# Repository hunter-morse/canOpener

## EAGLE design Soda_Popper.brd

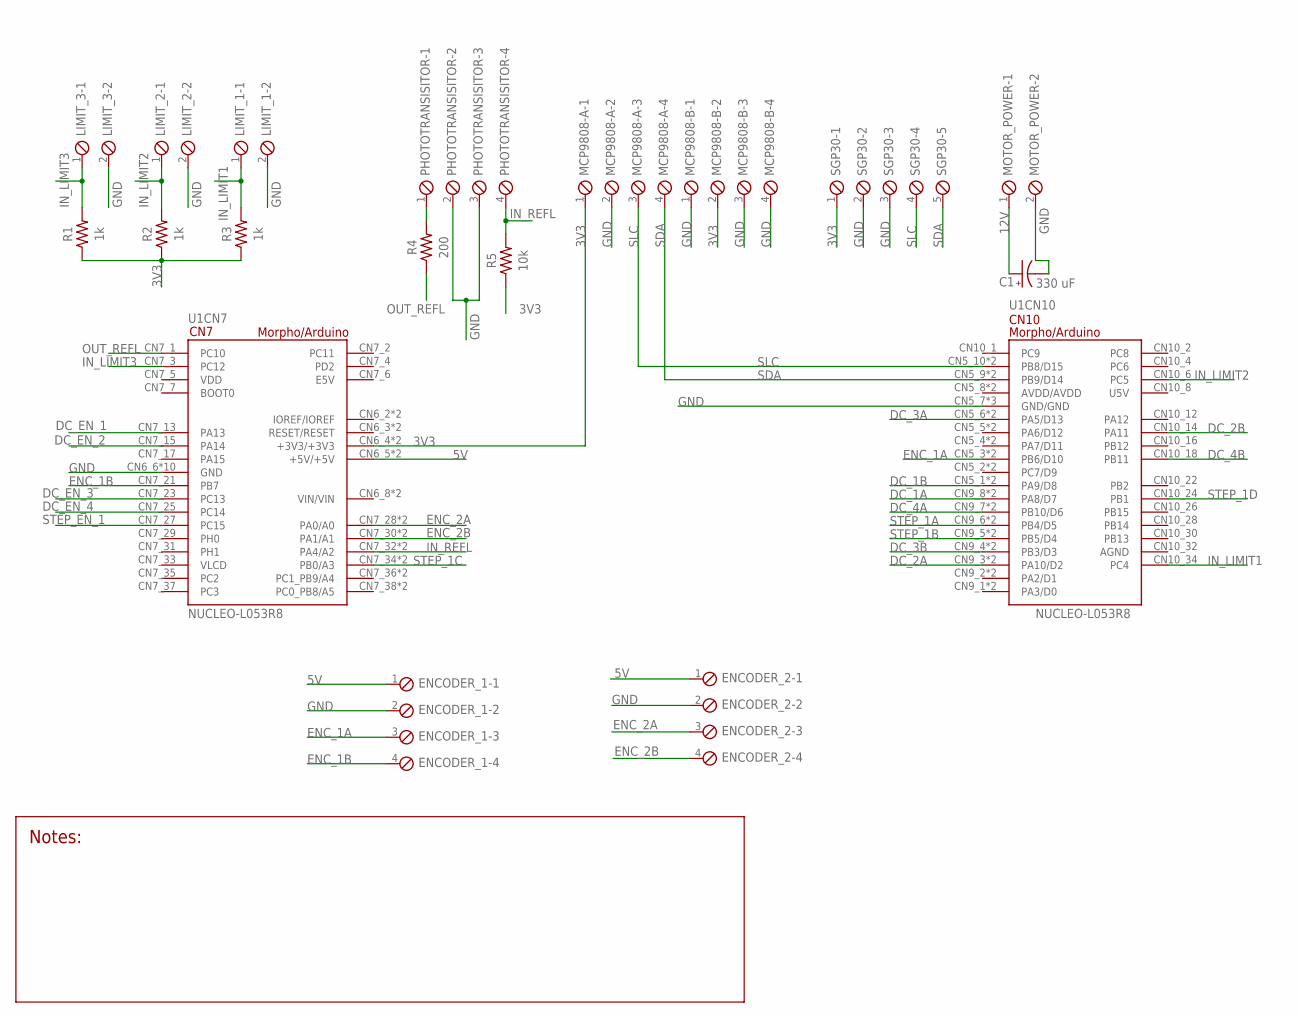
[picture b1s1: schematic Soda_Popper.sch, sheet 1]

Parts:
C1: 330 uF; CAPPRD508W65D1000H1100B
ENCODER_1, ENCODER_2: SCREWTERM_4P_254; 4POL254
LIMIT_1, LIMIT_2, LIMIT_3: SCREWTERM_2P_254; 2POL254
MCP9808-A, MCP9808-B: SCREWTERM_4P_254; 4POL254
MOTOR_POWER: SCREWTERM_2P_508; 2POL508
PHOTOTRANSISITOR: SCREWTERM_4P_254; 4POL254
R1, R2, R3: 1k; RESC3216X70
R4: 200; RESC3216X70
R5: 10k; RESC2012X65
SGP30: SCREWTERM_5P_254; 5POL254
U1: NUCLEO-L053R8; MODULE_NUCLEO-L053R8

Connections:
3V3: MCP9808-A.1, MCP9808-B.2, R1.1, R2.1, R3.1, R5.1, SGP30.1, U1.CN6_4 (+3V3/+3V3), U1.CN7_16 (+3V3/+3V3)
5V: ENCODER_1.1, ENCODER_2.1, U1.CN6_5 (+5V/+5V), U1.CN7_18 (+5V/+5V); also elsewhere on the board
12V: C1.1 (+), MOTOR_POWER.1; also elsewhere on the board
DC_1A: U1.CN9_8 (PA8/D7), U1.CN10_23 (PA8/D7); also elsewhere on the board
DC_1B: U1.CN5_1 (PA9/D8), U1.CN10_21 (PA9/D8); also elsewhere on the board
DC_2A: U1.CN9_3 (PA10/D2), U1.CN10_33 (PA10/D2); also elsewhere on the board
DC_2B: U1.CN10_14 (PA11); also elsewhere on the board
DC_3A: U1.CN5_6 (PA5/D13), U1.CN10_11 (PA5/D13); also elsewhere on the board
DC_3B: U1.CN9_4 (PB3/D3), U1.CN10_31 (PB3/D3); also elsewhere on the board
DC_4A: U1.CN9_7 (PB10/D6), U1.CN10_25 (PB10/D6); also elsewhere on the board
DC_4B: U1.CN10_18 (PB11); also elsewhere on the board
DC_EN_1: U1.CN7_13 (PA13); also elsewhere on the board
DC_EN_2: U1.CN7_15 (PA14); also elsewhere on the board
DC_EN_3: U1.CN7_23 (PC13); also elsewhere on the board
DC_EN_4: U1.CN7_25 (PC14); also elsewhere on the board
ENC_1A: ENCODER_1.3, U1.CN5_3 (PB6/D10), U1.CN10_17 (PB6/D10)
ENC_1B: ENCODER_1.4, U1.CN7_21 (PB7)
ENC_2A: ENCODER_2.3, U1.CN7_28 (PA0/A0), U1.CN8_1 (PA0/A0)
ENC_2B: ENCODER_2.4, U1.CN7_30 (PA1/A1), U1.CN8_2 (PA1/A1)
GND: C1.2 (-), ENCODER_1.2, ENCODER_2.2, LIMIT_1.2, LIMIT_2.2, LIMIT_3.2, MCP9808-A.2, MCP9808-B.1, MCP9808-B.3, MCP9808-B.4, MOTOR_POWER.2, PHOTOTRANSISITOR.2, PHOTOTRANSISITOR.3, SGP30.2, SGP30.3, U1.CN5_7 (GND/GND), U1.CN6_6 (GND), U1.CN6_7 (GND), U1.CN7_8 (GND), U1.CN7_19 (GND), U1.CN7_20 (GND), U1.CN7_22 (GND), U1.CN10_9 (GND/GND), U1.CN10_20 (GND/GND), U1.CN11_1 (GND), U1.CN11_2 (GND), U1.CN12_1 (GND), U1.CN12_2 (GND); also elsewhere on the board
IN_LIMIT1: LIMIT_1.1, R3.2, U1.CN10_34 (PC4)
IN_LIMIT2: LIMIT_2.1, R2.2, U1.CN10_6 (PC5)
IN_LIMIT3: LIMIT_3.1, R1.2, U1.CN7_3 (PC12)
IN_REFL: PHOTOTRANSISITOR.4, R5.2, U1.CN7_32 (PA4/A2), U1.CN8_3 (PA4/A2)
unnamed: PHOTOTRANSISITOR.1, R4.2
OUT_REFL: R4.1, U1.CN7_1 (PC10)
SDA: MCP9808-A.4, SGP30.5, U1.CN5_9 (PB9/D14), U1.CN10_5 (PB9/D14)
SLC: MCP9808-A.3, SGP30.4, U1.CN5_10 (PB8/D15), U1.CN10_3 (PB8/D15)
STEP_1A: U1.CN9_6 (PB4/D5), U1.CN10_27 (PB4/D5); also elsewhere on the board
STEP_1B: U1.CN9_5 (PB5/D4), U1.CN10_29 (PB5/D4); also elsewhere on the board
STEP_1C: U1.CN7_34 (PB0/A3), U1.CN8_4 (PB0/A3); also elsewhere on the board
STEP_1D: U1.CN10_24 (PB1); also elsewhere on the board
STEP_EN_1: U1.CN7_27 (PC15); also elsewhere on the board

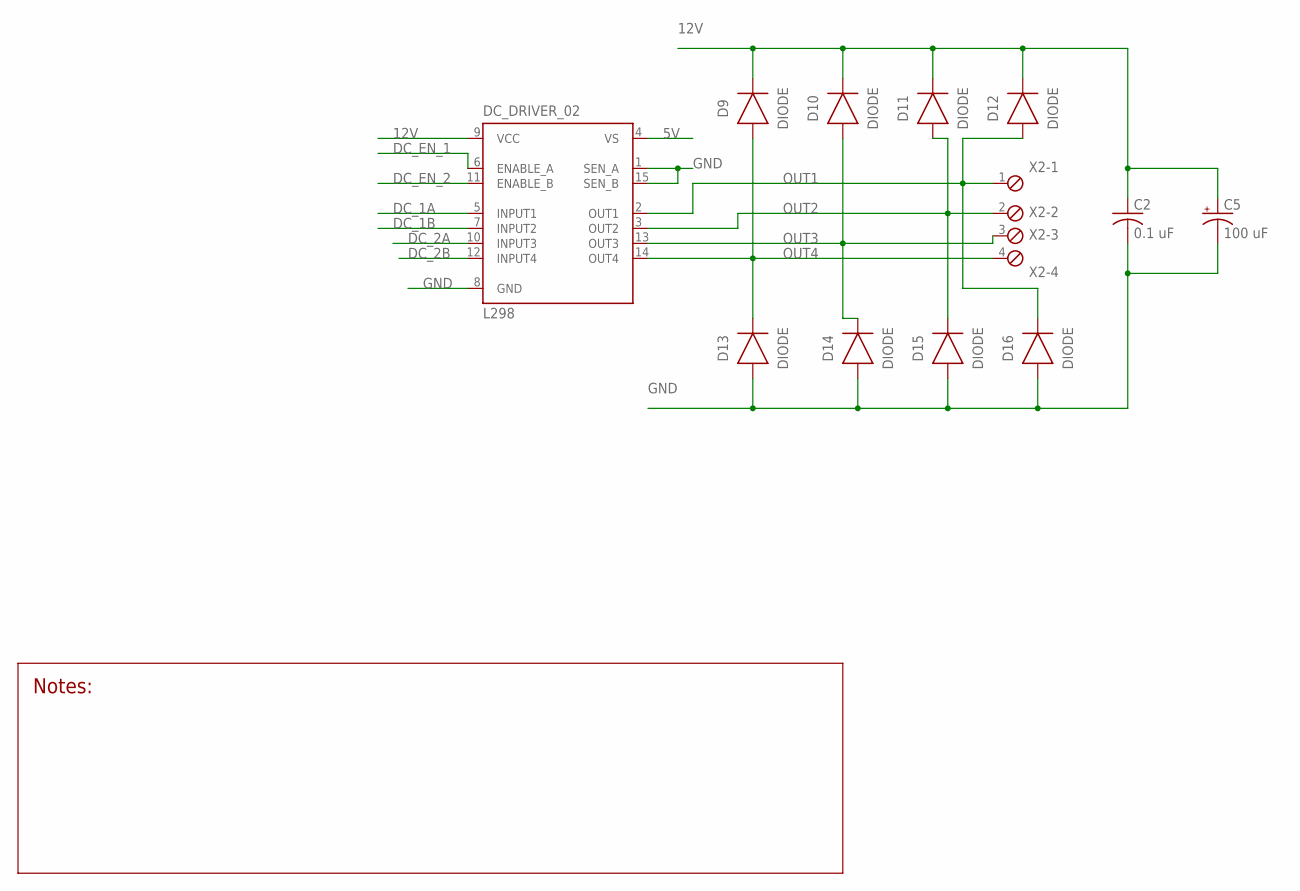
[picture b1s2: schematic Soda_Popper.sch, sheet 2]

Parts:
C2: 0.1 uF; CAPC2012X110
C5: 100 uF; CAPPRD508W65D1000H1100B
D9, D10, D11, D12, D13, D14, D15, D16: DIODE; DIOM5336X265N
DC_DRIVER_02: L298; MULTIWATT-15
X2: SCREWTERM_4P_508; 4POL508

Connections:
5V: DC_DRIVER_02.4 (VS); also elsewhere on the board
12V: C2.1, C5.1 (+), D9.1 (C), D10.1 (C), D11.1 (C), D12.1 (C), DC_DRIVER_02.9 (VCC); also elsewhere on the board
DC_1A: DC_DRIVER_02.5 (INPUT1); also elsewhere on the board
DC_1B: DC_DRIVER_02.7 (INPUT2); also elsewhere on the board
DC_2A: DC_DRIVER_02.10 (INPUT3); also elsewhere on the board
DC_2B: DC_DRIVER_02.12 (INPUT4); also elsewhere on the board
DC_EN_1: DC_DRIVER_02.6 (ENABLE_A); also elsewhere on the board
DC_EN_2: DC_DRIVER_02.11 (ENABLE_B); also elsewhere on the board
GND: C2.2, C5.2 (-), D13.2 (A), D14.2 (A), D15.2 (A), D16.2 (A), DC_DRIVER_02.1 (SEN_A), DC_DRIVER_02.8 (GND), DC_DRIVER_02.15 (SEN_B); also elsewhere on the board
OUT1: D12.2 (A), D16.1 (C), DC_DRIVER_02.2 (OUT1), X2.1
OUT2: D11.2 (A), D15.1 (C), DC_DRIVER_02.3 (OUT2), X2.2
OUT3: D10.2 (A), D14.1 (C), DC_DRIVER_02.13 (OUT3), X2.3
OUT4: D9.2 (A), D13.1 (C), DC_DRIVER_02.14 (OUT4), X2.4

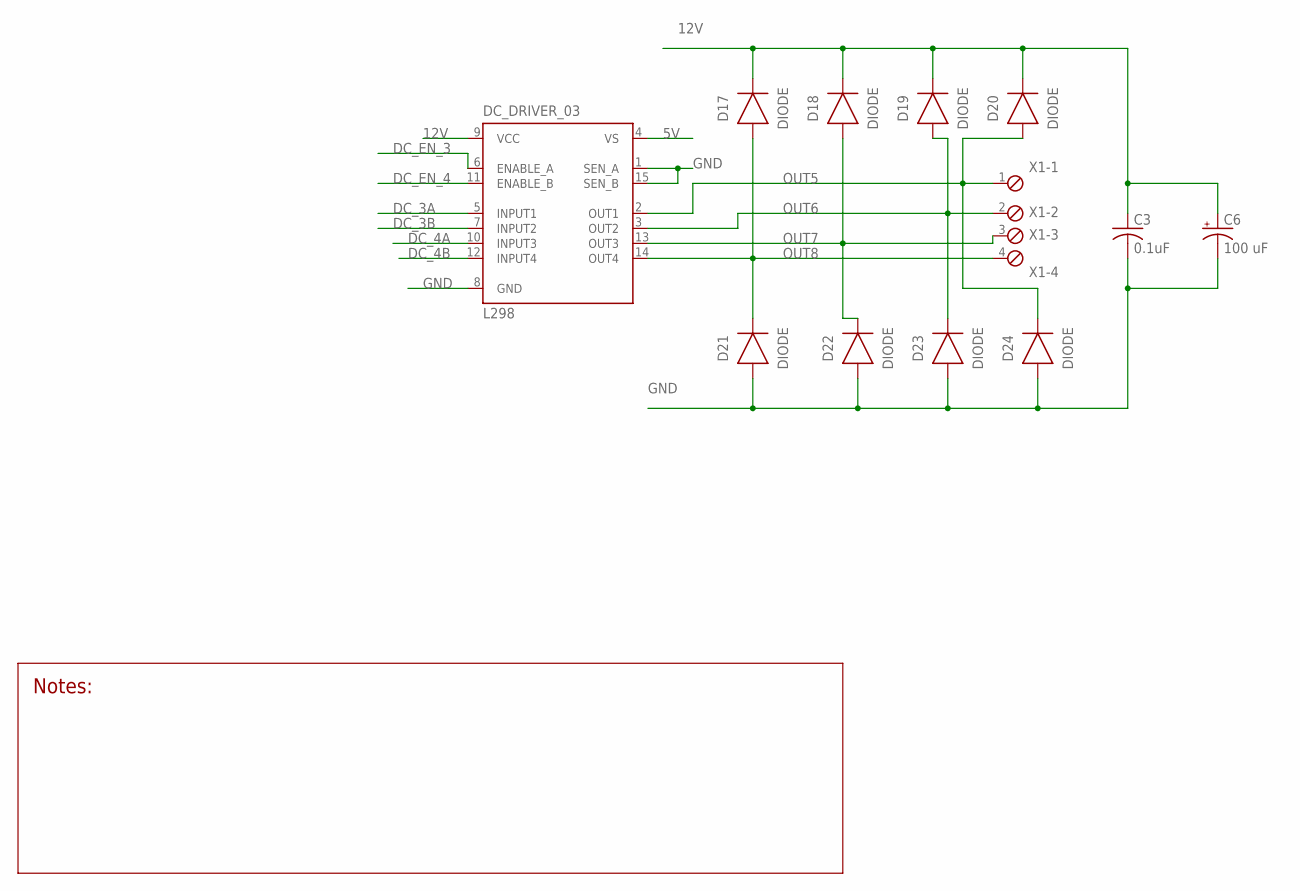
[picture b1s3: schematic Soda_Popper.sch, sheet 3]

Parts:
C3: 0.1uF; CAPC2012X110
C6: 100 uF; CAPPRD508W65D1000H1100B
D17, D18, D19, D20, D21, D22, D23, D24: DIODE; DIOM5336X265N
DC_DRIVER_03: L298; MULTIWATT-15
X1: SCREWTERM_4P_508; 4POL508

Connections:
5V: DC_DRIVER_03.4 (VS); also elsewhere on the board
12V: C3.1, C6.1 (+), D17.1 (C), D18.1 (C), D19.1 (C), D20.1 (C), DC_DRIVER_03.9 (VCC); also elsewhere on the board
DC_3A: DC_DRIVER_03.5 (INPUT1); also elsewhere on the board
DC_3B: DC_DRIVER_03.7 (INPUT2); also elsewhere on the board
DC_4A: DC_DRIVER_03.10 (INPUT3); also elsewhere on the board
DC_4B: DC_DRIVER_03.12 (INPUT4); also elsewhere on the board
DC_EN_3: DC_DRIVER_03.6 (ENABLE_A); also elsewhere on the board
DC_EN_4: DC_DRIVER_03.11 (ENABLE_B); also elsewhere on the board
GND: C3.2, C6.2 (-), D21.2 (A), D22.2 (A), D23.2 (A), D24.2 (A), DC_DRIVER_03.1 (SEN_A), DC_DRIVER_03.8 (GND), DC_DRIVER_03.15 (SEN_B); also elsewhere on the board
OUT5: D20.2 (A), D24.1 (C), DC_DRIVER_03.2 (OUT1), X1.1
OUT6: D19.2 (A), D23.1 (C), DC_DRIVER_03.3 (OUT2), X1.2
OUT7: D18.2 (A), D22.1 (C), DC_DRIVER_03.13 (OUT3), X1.3
OUT8: D17.2 (A), D21.1 (C), DC_DRIVER_03.14 (OUT4), X1.4

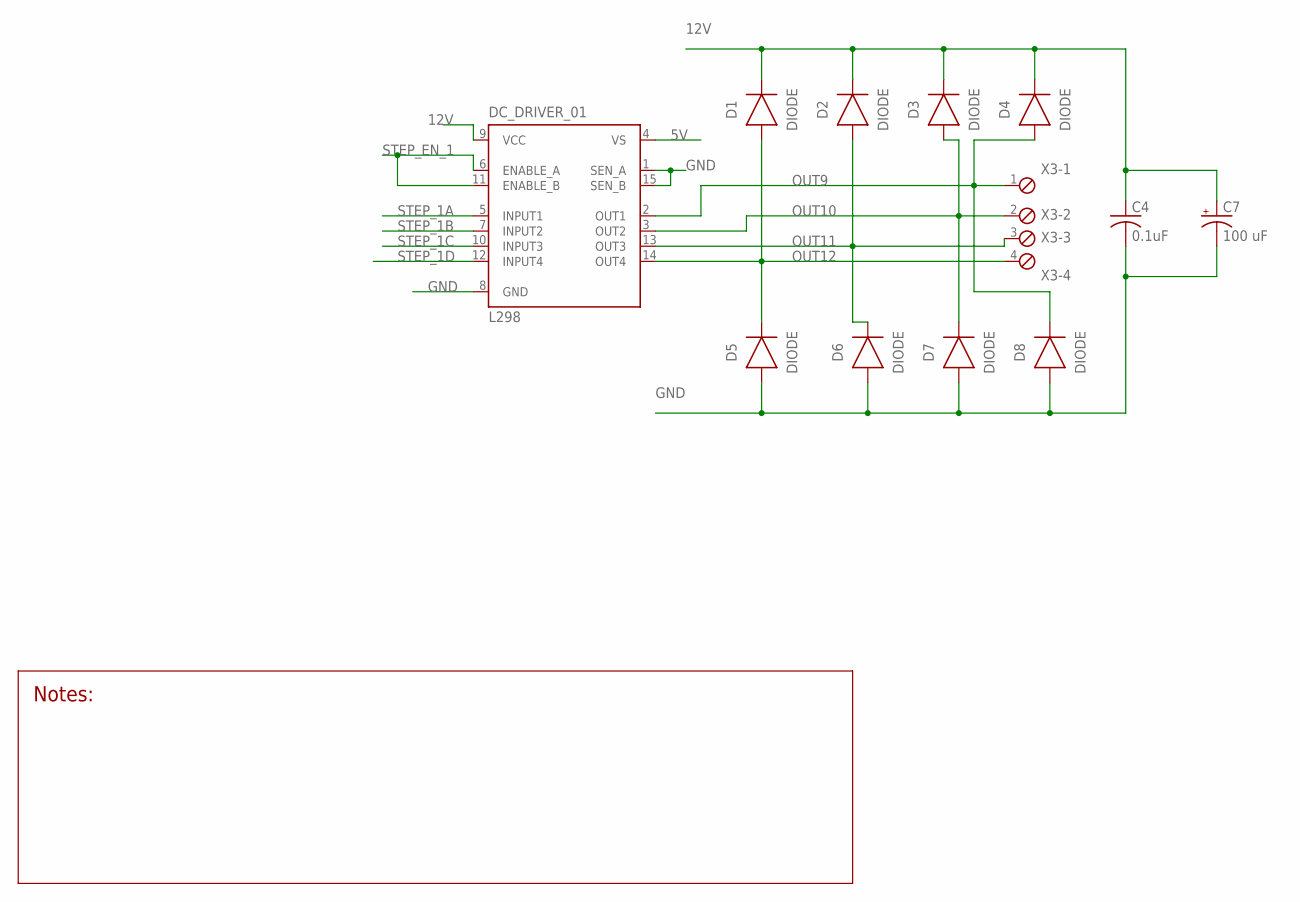
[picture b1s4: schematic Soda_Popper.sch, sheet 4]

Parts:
C4: 0.1uF; CAPC2012X110
C7: 100 uF; CAPPRD508W65D1000H1100B
D1, D2, D3, D4, D5, D6, D7, D8: DIODE; DIOM5336X265N
DC_DRIVER_01: L298; MULTIWATT-15
X3: SCREWTERM_4P_508; 4POL508

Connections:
5V: DC_DRIVER_01.4 (VS); also elsewhere on the board
12V: C4.1, C7.1 (+), D1.1 (C), D2.1 (C), D3.1 (C), D4.1 (C), DC_DRIVER_01.9 (VCC); also elsewhere on the board
GND: C4.2, C7.2 (-), D5.2 (A), D6.2 (A), D7.2 (A), D8.2 (A), DC_DRIVER_01.1 (SEN_A), DC_DRIVER_01.8 (GND), DC_DRIVER_01.15 (SEN_B); also elsewhere on the board
OUT9: D4.2 (A), D8.1 (C), DC_DRIVER_01.2 (OUT1), X3.1
OUT10: D3.2 (A), D7.1 (C), DC_DRIVER_01.3 (OUT2), X3.2
OUT11: D2.2 (A), D6.1 (C), DC_DRIVER_01.13 (OUT3), X3.3
OUT12: D1.2 (A), D5.1 (C), DC_DRIVER_01.14 (OUT4), X3.4
STEP_1A: DC_DRIVER_01.5 (INPUT1); also elsewhere on the board
STEP_1B: DC_DRIVER_01.7 (INPUT2); also elsewhere on the board
STEP_1C: DC_DRIVER_01.10 (INPUT3); also elsewhere on the board
STEP_1D: DC_DRIVER_01.12 (INPUT4); also elsewhere on the board
STEP_EN_1: DC_DRIVER_01.6 (ENABLE_A), DC_DRIVER_01.11 (ENABLE_B); also elsewhere on the board

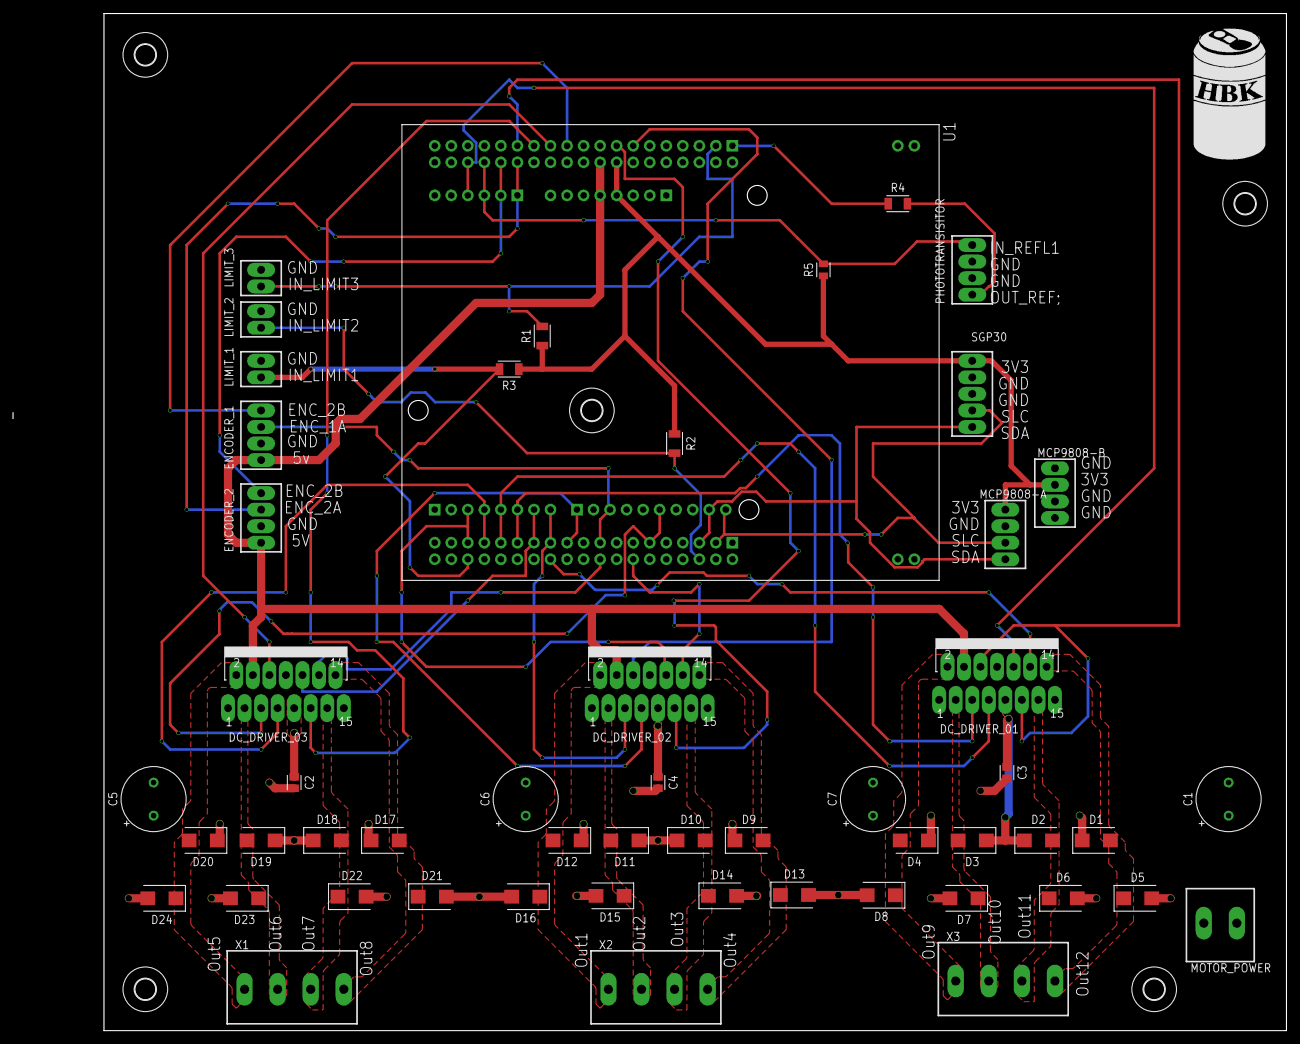
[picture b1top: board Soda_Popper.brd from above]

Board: 2 copper layers, 195.5 x 156.2 mm, 58 parts (0 on the bottom side), 45 nets.

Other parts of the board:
U$1, U$2, U$3, U$4, U$5: 3,2

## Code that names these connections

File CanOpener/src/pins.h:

/**
 * @file    pins.h
 *          Definition of all pins used
 * @author  Hunter Morse
 * @date    Nov xx, 2021
 */ 

#ifndef PINS_H
#define PINS_H

/**
 * @cond
 * */
// DC Motor 1
#define DC1a    PA8 //TIM1
#define DC1b    PA9
#define DCEN1   PA13

// DC Motor 2
#define DC2a    PA10 //TIM1
#define DC2b    PA11
#define DCEN2   PA14

// DC Motor 3
#define DC3a    PA5 //TIM2
#define DC3b    PB3
#define DCEN3   PC13

// DC Motor 4
#define DC4a    PB10 //TIM2
#define DC4b    PB11
#define DCEN4   PC14

// Stepper Motor 1
#define STEP1a  PB4 //TIM3
#define STEP1b  PB5
#define STEP1c  PB0
#define STEP1d  PB1
#define STEP1EN PC15

// Limit Switches
#define INLIM1  PC4
#define INLIM2  PC5
#define INLIM3  PC12

// Encoders
#define ENC1a   PB6 //TIM4
#define ENC1b   PB7
#define ENC1TIM TIM4
#define ENC2a   PA0 //TIM5
#define ENC2b   PA1
#define ENC2TIM TIM5

// Reflective Sensor
#define OUT_REFL PC10
#define IN_REFL PA4

#endif
/**
 * @endcond
 * */

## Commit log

2021-10-07 Nucleo-L476RG PlatformIO project initialized
2021-11-11 Example of using the Wire class to perform I2C comms
2021-11-15 Created a working driver for the MCP9808 temperature sensor
2021-11-18 Beginning of Stepper Motor Driver
2021-11-18 Added all functions to the Stepper Motor Driver - This was done in class so I will go back to look at it closer
2021-11-18 Added some old test files from Ben's local machine
2021-11-18 Started documentation for the StepperDriver class
2021-11-19 Finished documentation for the StepperDriver class
2021-11-19 Started on servo motor driver
2021-11-20 Added major functionality to the MotorDriver class. At this point there are no getters or setters, and the code needs to be tested
2021-11-27 motor driver
2021-11-28 Started work on the temp sensor task
2021-11-28 Created the shares.h file
2021-11-28 Created the taskTemp files
2021-11-28 Working on tasks. Seems to have some errors with taskShare.h
2021-11-29 Fixed compile errors - needed more includes and reorder of the ones that were there
2021-11-29 Added getters to the MotorDriver class
2021-11-29 Checked functionality of the MotorDriver class
2021-11-29 Tested StepperDriver class
2021-11-30 reorganized. moved tthe test main to misc
2021-11-30 Testing the stepper motor
2021-11-30 This main file is now ready for testing the stepper motor
2021-11-30 Updated include paths
2021-11-30 Added main.cpp and fixed include errors at compile
2021-11-30 Moved some files around
2021-11-30 Documentation for the MotorDriver class
2021-11-30 Documentation for the Temp Sensor class
2021-11-30 Added the doxyfile and created the docs folder for Github page
2021-11-30 Fixed some documentation
2021-12-01 working on tasks
2021-12-01 current limit switch task is more of a machine operation task so I need to switch that around
2021-12-01 limitSwitch task complete and machine move task in the works. project currently compiles without errors
2021-12-01 Add files via upload
    Photointerrupt task
2021-12-01 Added some tasks to the main.cpp file. Also tested compiling and it compiled
2021-12-01 taskMoveMachine.cpp updated
2021-12-01 Added encoders to pins.h
2021-12-01 Added delay
2021-12-01 Created the taskEncoder task
2021-12-01 Working on documentation
2021-12-02 Changed some things on the taskMoveMachine.cpp
2021-12-02 fixed encoder compile
2021-12-02 Redid Photosensor project from Kyle's upload
2021-12-02 At this moment, a lot is commented out but the limit switches are working
2021-12-02 figuring out why upload won't work
2021-12-02 "not sure"
2021-12-02 Working Stepper motor
2021-12-02 This is currently working. Using 2 limit switches, we can control moving the platform down, and then moving it back up. Next step is working on the photo interrupt
2021-12-02 Got the base rotating
2021-12-02 Photosensor working
2021-12-02 Added kill switch and platform raise. Working at this point
2021-12-02 Slight mod to taskTemp
2021-12-07 reset motor base changes pushed
2021-12-07 commented all taks files
2021-12-07 Set theme jekyll-theme-minimal
2021-12-07 Added board and schematic
2021-12-08 Documentation stuffs
2021-12-08 Documentation
2021-12-08 Doxygen
2021-12-08 added intro, logo, video
